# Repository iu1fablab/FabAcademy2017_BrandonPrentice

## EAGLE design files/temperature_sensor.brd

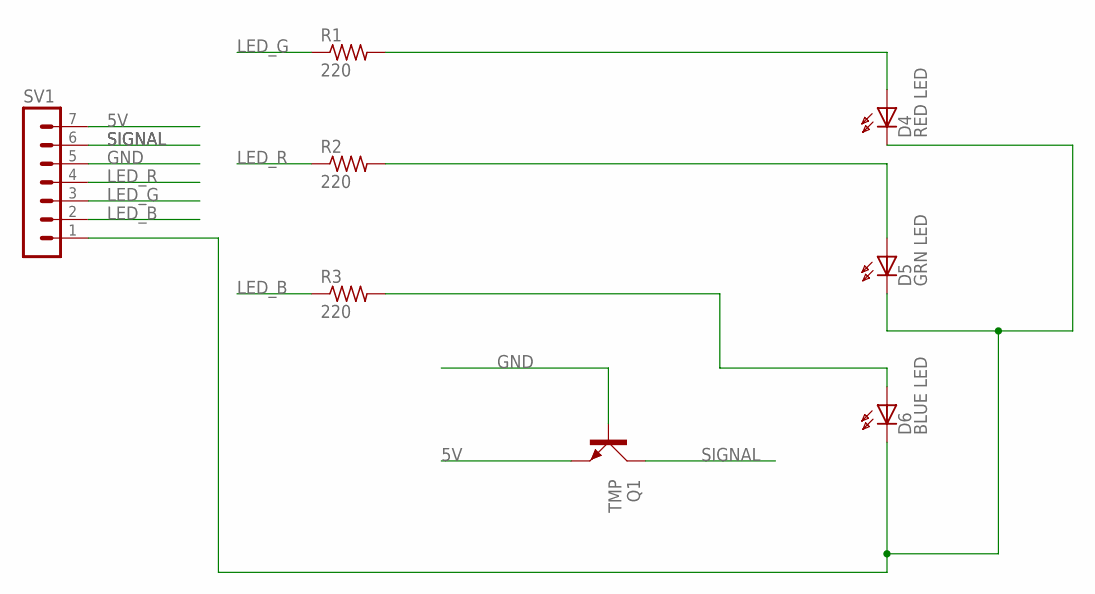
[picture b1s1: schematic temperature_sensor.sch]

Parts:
D4: RED LED; HLMP6
D5: GRN LED; HLMP6
D6: BLUE LED; HLMP6
Q1: TMP; TO126AV
R1, R2, R3: 220; R1206
SV1: MA07-1

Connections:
5V: Q1.E, SV1.7
GND: Q1.B, SV1.5
GND2: D4.K, D5.K, D6.K, SV1.1
LED_B: R3.1, SV1.2
LED_G: R1.1, SV1.3
LED_R: R2.1, SV1.4
unnamed: D6.A, R3.2
unnamed: D5.A, R2.2
unnamed: D4.A, R1.2
SIGNAL: Q1.C, SV1.6

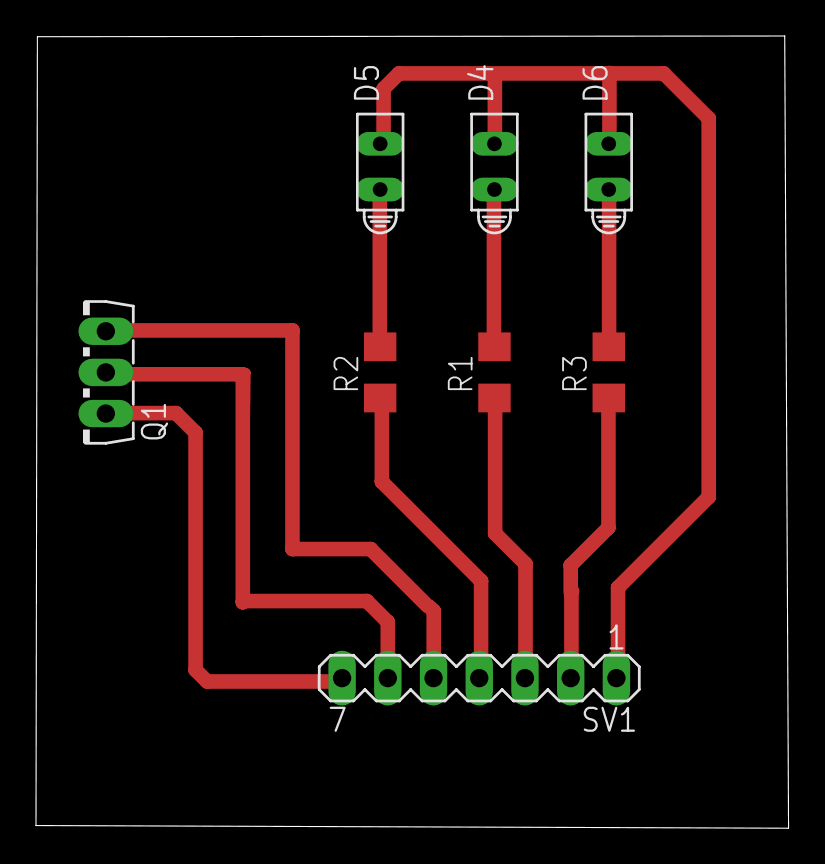
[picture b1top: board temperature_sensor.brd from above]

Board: 2 copper layers, 41.8 x 44.0 mm, 8 parts (0 on the bottom side), 10 nets.

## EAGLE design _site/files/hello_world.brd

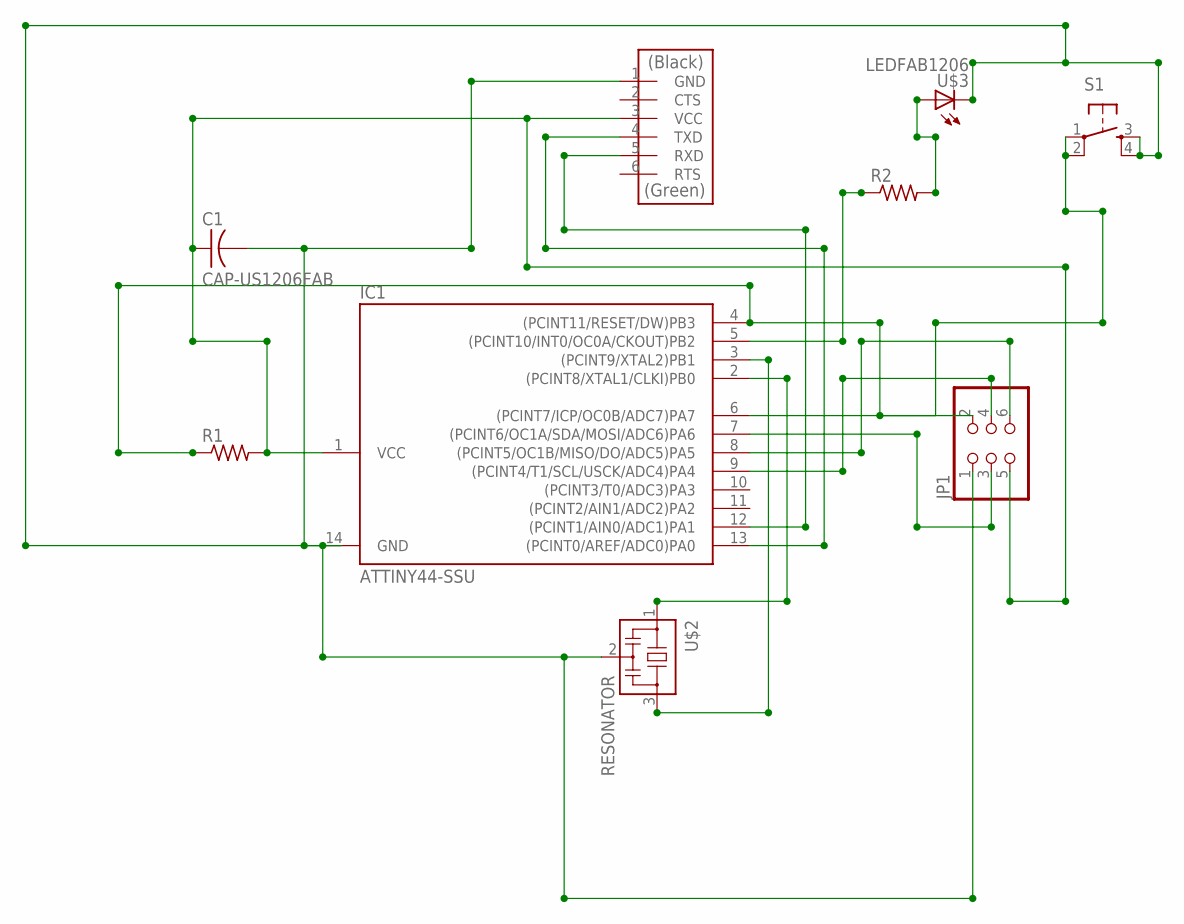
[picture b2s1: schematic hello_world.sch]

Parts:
C1: CAP-US1206FAB; C1206FAB
IC1: ATTINY44-SSU; SOIC14
JP1: PINHD-2X3-SMD; 2X03SMD
R1, R2: RES-US1206FAB; R1206FAB
S1: 6MM_SWITCH6MM_SWITCH; 6MM_SWITCH
U$1: FTDI-SMD-HEADER; 1X06SMD
U$2: RESONATOR; EFOBM
U$3: LEDFAB1206; LED1206FAB

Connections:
unnamed: C1.1, IC1.1 (VCC), IC1.13 ((PCINT0/AREF/ADC0)PA0), JP1.5, R1.2, U$1.3 (VCC), U$1.4 (TXD)
unnamed: IC1.9 ((PCINT4/T1/SCL/USCK/ADC4)PA4), JP1.4
unnamed: IC1.7 ((PCINT6/OC1A/SDA/MOSI/ADC6)PA6), JP1.3
unnamed: IC1.4 ((PCINT11/RESET/DW)PB3), JP1.2, R1.1
unnamed: IC1.12 ((PCINT1/AIN0/ADC1)PA1), U$1.5 (RXD)
unnamed: IC1.2 ((PCINT8/XTAL1/CLKI)PB0), U$2.1
unnamed: IC1.3 ((PCINT9/XTAL2)PB1), U$2.3
unnamed: C1.2, IC1.14 (GND), JP1.1, U$1.1 (GND), U$2.2
unnamed: IC1.8 ((PCINT5/OC1B/MISO/DO/ADC5)PA5), JP1.6
unnamed: IC1.5 ((PCINT10/INT0/OC0A/CKOUT)PB2), R2.1
unnamed: IC1.6 ((PCINT7/ICP/OC0B/ADC7)PA7), S1.1, S1.2 (P1)
unnamed: R2.2, U$3.1 (A)
unnamed: S1.3 (S), S1.4 (S1), U$3.2 (C)

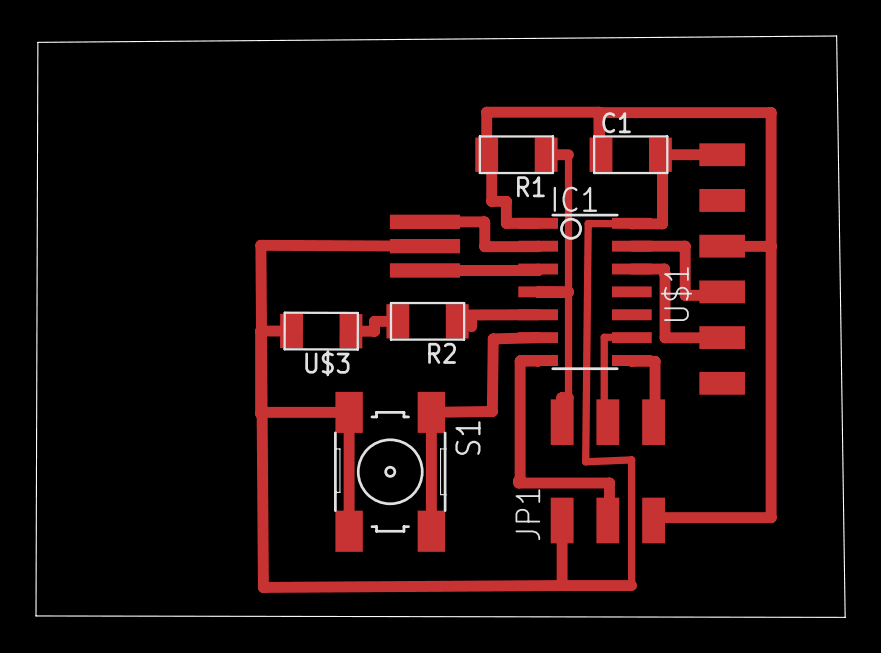
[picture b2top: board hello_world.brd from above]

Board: 2 copper layers, 45.0 x 32.3 mm, 9 parts (0 on the bottom side), 13 nets.

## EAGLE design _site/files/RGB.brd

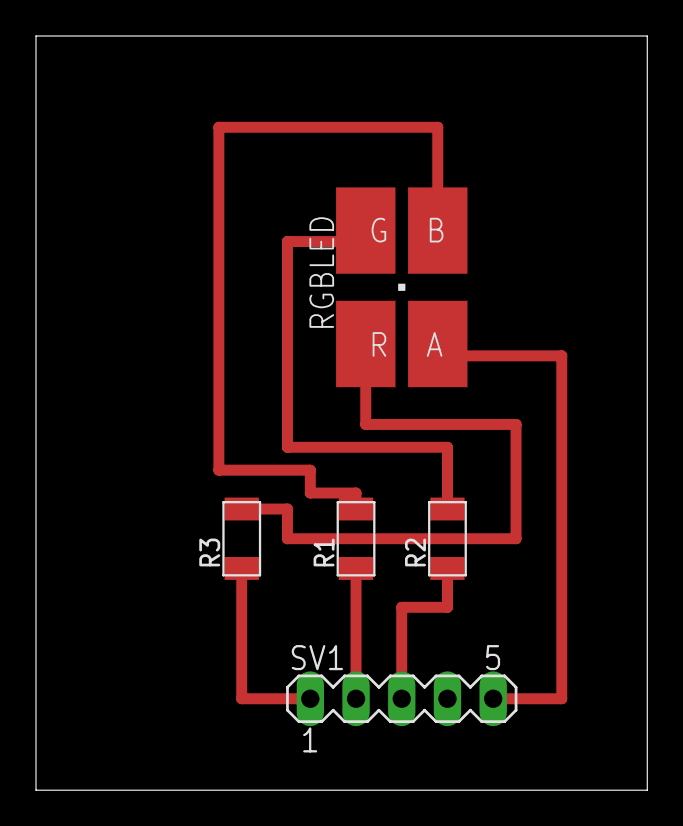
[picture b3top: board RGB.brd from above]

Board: 2 copper layers, 34.0 x 41.9 mm, 5 parts (0 on the bottom side), 7 nets.

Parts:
R1, R2: 10K; R1206FAB
R3: 499ohm; R1206FAB
RGBLED: LEDRGBNEW; P-LCC-4
SV1: MA05-1

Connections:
unnamed: RGBLED.A, SV1.5
unnamed: R3.2, RGBLED.R
unnamed: R3.1, SV1.1
unnamed: R1.2, RGBLED.B
unnamed: R1.1, SV1.2
unnamed: R2.2, RGBLED.G
unnamed: R2.1, SV1.3

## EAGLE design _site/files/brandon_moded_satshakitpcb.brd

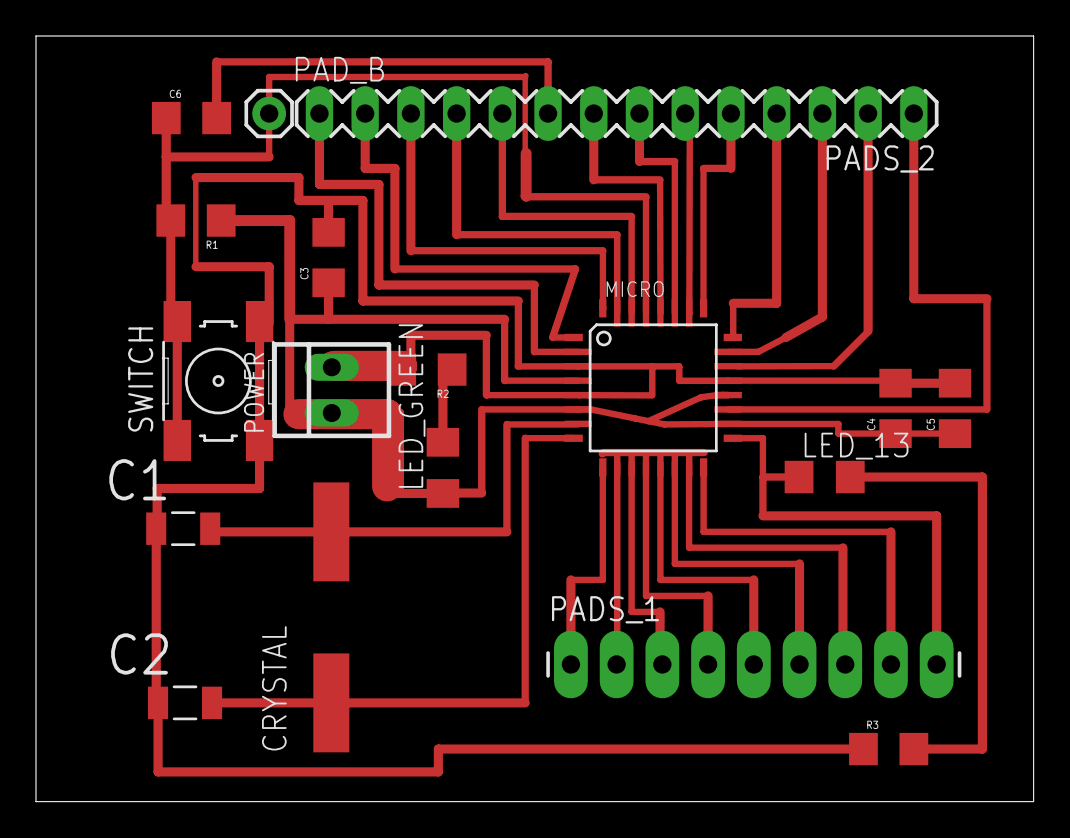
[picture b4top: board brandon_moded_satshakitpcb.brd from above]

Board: 2 copper layers, 55.4 x 42.5 mm, 18 parts (0 on the bottom side), 30 nets.

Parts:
C1, C2: 22pF; CAPC3216X178N
C3: 10uF; 1206
C4: 1uF; 1206
C5, C6: 100nF; 1206
CRYSTAL: 16Mhz; CSM-7X-DU
LED_13: YELLOW; 1206
LED_GREEN: 1206
MICRO: ATMEGA328P-AU; TQFP32-08
PADS_1: M09LONGPADS; 1X09_LONGPADS
PADS_2: M14LONGPADS; 1X14-LONGPADS
PAD_B: M01PTH; 1X01
POWER: 22-23-2021
R1: 10k; 1206
R2, R3: 499; 1206
SWITCH: 6MM_SWITCH

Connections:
GND: C1.1, C2.1, R3.1, SWITCH.3, SWITCH.4
unnamed: MICRO.9, PADS_1.1
unnamed: C1.2, CRYSTAL.2, MICRO.7
unnamed: C6.2, PADS_2.9
unnamed: MICRO.10, PADS_1.2
unnamed: MICRO.11, PADS_1.3
unnamed: MICRO.12, PADS_1.4
unnamed: MICRO.13, PADS_1.5
unnamed: MICRO.14, PADS_1.6
unnamed: C2.2, CRYSTAL.1, MICRO.8
unnamed: MICRO.16, PADS_1.8
unnamed: LED_13.1, MICRO.17, PADS_1.9
unnamed: MICRO.19, PADS_2.1
unnamed: MICRO.23, PADS_2.3
unnamed: MICRO.24, PADS_2.4
unnamed: MICRO.25, PADS_2.5
unnamed: MICRO.26, PADS_2.6
unnamed: MICRO.27, PADS_2.7
unnamed: MICRO.30, PADS_2.10
unnamed: MICRO.31, PADS_2.11
unnamed: MICRO.32, PADS_2.12
unnamed: MICRO.1, PADS_2.13
unnamed: MICRO.2, PADS_2.14
unnamed: MICRO.28, PADS_2.8
unnamed: LED_GREEN.2, R2.1
unnamed: LED_13.2, R3.2
unnamed: C6.1, PAD_B.1, R1.2, SWITCH.1, SWITCH.2
S$3: POWER.2, R2.2
S$8: C4.2, C5.2, MICRO.21
VCC: C3.1, LED_GREEN.1, MICRO.4, MICRO.6, MICRO.18, MICRO.20, POWER.1, R1.1

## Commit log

2017-12-21 Initial commit of Brandon Prentice website
2017-12-21 Updated baseurl in config.yml to remove FabAcademy gitlab URL structure

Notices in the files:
parts and their libraries:
01_SparkFun: Licensing: CC v3.0 Share-Alike You are welcome to use this library for commercial purposes.
